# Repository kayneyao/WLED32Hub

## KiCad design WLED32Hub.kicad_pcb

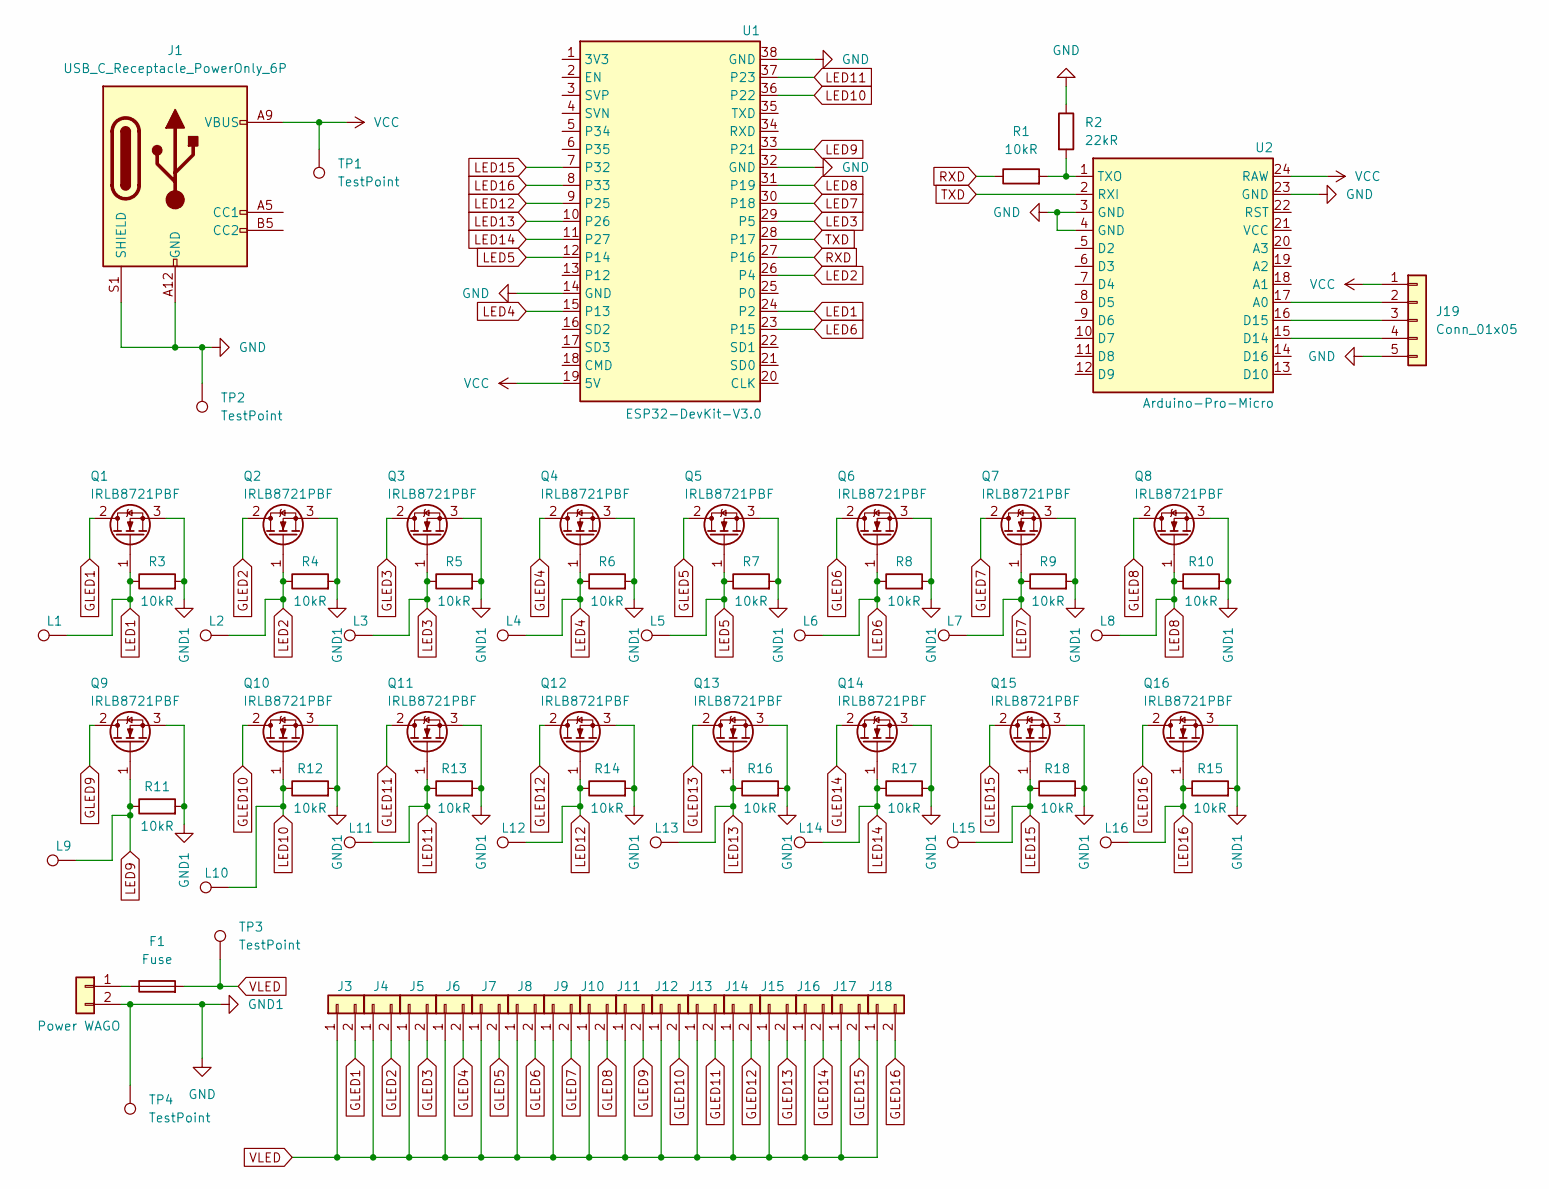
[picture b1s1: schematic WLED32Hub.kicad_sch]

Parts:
F1: Fuse; Fuseholder_Blade_ATO_Littelfuse_Pudenz_2_Pin
J1: USB_C_Receptacle_PowerOnly_6P; USB_C_Receptacle_GCT_USB4125-xx-x-0190_6P_TopMnt_Horizontal
J2: Power WAGO; WAGO_2606-1102
J3, J4, J5, J6, J7, J8, J9, J10, J11, J12, J13, J14, J15, J16, J17, J18: WAGO; TerminalBlock_WAGO_2601-1102_1x02_P3.50mm_Horizontal
J19: Conn_01x05; SolderWirePad_1x05_SMD_1x2mm
L1, L2, L3, L4, L5, L6, L7, L8, L9, L10, L11, L12, L13, L14, L15, L16: TestPoint; TestPoint_Pad_1.5x1.5mm
Q1, Q2, Q3, Q4, Q5, Q6, Q7, Q8, Q9, Q10, Q11, Q12, Q13, Q14, Q15, Q16: IRLB8721PBF; TO-220-3_Vertical
R1, R3, R4, R5, R6, R7, R8, R9, R10, R11, R12, R13, R14, R15, R16, R17, R18: 10kR; R_Axial_DIN0309_L9.0mm_D3.2mm_P12.70mm_Horizontal
R2: 22kR; R_Axial_DIN0309_L9.0mm_D3.2mm_P12.70mm_Horizontal
TP1, TP2, TP3, TP4: TestPoint; TestPoint_Pad_1.5x1.5mm
U1: ESP32-DevKit-V3.0; ESP32_DevKit_V3.0
U2: Arduino-Pro-Micro; Arduino_Pro_Micro

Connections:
GLED1: J3.2, Q1.2 (D)
GLED2: J4.2, Q2.2 (D)
GLED3: J5.2, Q3.2 (D)
GLED4: J6.2, Q4.2 (D)
GLED5: J7.2, Q5.2 (D)
GLED6: J8.2, Q6.2 (D)
GLED7: J9.2, Q7.2 (D)
GLED8: J10.2, Q8.2 (D)
GLED9: J11.2, Q9.2 (D)
GLED10: J12.2, Q10.2 (D)
GLED11: J13.2, Q11.2 (D)
GLED12: J14.2, Q12.2 (D)
GLED13: J15.2, Q13.2 (D)
GLED14: J16.2, Q14.2 (D)
GLED15: J17.2, Q15.2 (D)
GLED16: J18.2, Q16.2 (D)
GND: J1.A12 (GND), J1.B12 (GND), J1.S1 (SHIELD), J2.2, J19.5, Q1.3 (S), Q2.3 (S), Q3.3 (S), Q4.3 (S), Q5.3 (S), Q6.3 (S), Q7.3 (S), Q8.3 (S), Q9.3 (S), Q10.3 (S), Q11.3 (S), Q12.3 (S), Q13.3 (S), Q14.3 (S), Q15.3 (S), Q16.3 (S), R2.1, R3.2, R4.2, R5.2, R6.2, R7.2, R8.2, R9.2, R10.2, R11.2, R12.2, R13.2, R14.2, R15.2, R16.2, R17.2, R18.2, TP2.1, TP4.1, U1.14 (GND), U1.32 (GND), U1.38 (GND), U2.3 (GND), U2.4 (GND), U2.23 (GND); also elsewhere on the board
LED1: L1.1, Q1.1 (G), R3.1, U1.24 (P2)
LED2: L2.1, Q2.1 (G), R4.1, U1.26 (P4)
LED3: L3.1, Q3.1 (G), R5.1, U1.29 (P5)
LED4: L4.1, Q4.1 (G), R6.1, U1.15 (P13)
LED5: L5.1, Q5.1 (G), R7.1, U1.12 (P14)
LED6: L6.1, Q6.1 (G), R8.1, U1.23 (P15)
LED7: L7.1, Q7.1 (G), R9.1, U1.30 (P18)
LED8: L8.1, Q8.1 (G), R10.1, U1.31 (P19)
LED9: L9.1, Q9.1 (G), R11.1, U1.33 (P21)
LED10: L10.1, Q10.1 (G), R12.1, U1.36 (P22)
LED11: L11.1, Q11.1 (G), R13.1, U1.37 (P23)
LED12: L12.1, Q12.1 (G), R14.1, U1.9 (P25)
LED13: L13.1, Q13.1 (G), R16.1, U1.10 (P26)
LED14: L14.1, Q14.1 (G), R17.1, U1.11 (P27)
LED15: L15.1, Q15.1 (G), R18.1, U1.7 (P32)
LED16: L16.1, Q16.1 (G), R15.1, U1.8 (P33)
unnamed: F1.1, J2.1
unnamed: J19.2, U2.17 (A0)
unnamed: J19.3, U2.16 (D15)
unnamed: J19.4, U2.15 (D14)
unnamed: R1.2, R2.2, U2.1 (TXO)
RXD: R1.1, U1.27 (P16)
TXD: U1.28 (P17), U2.2 (RXI)
VCC: J1.A9 (VBUS), J1.B9 (VBUS), J19.1, TP1.1, U1.19 (5V), U2.24 (RAW)
VLED: F1.2, J3.1, J4.1, J5.1, J6.1, J7.1, J8.1, J9.1, J10.1, J11.1, J12.1, J13.1, J14.1, J15.1, J16.1, J17.1, J18.1, TP3.1; also elsewhere on the board

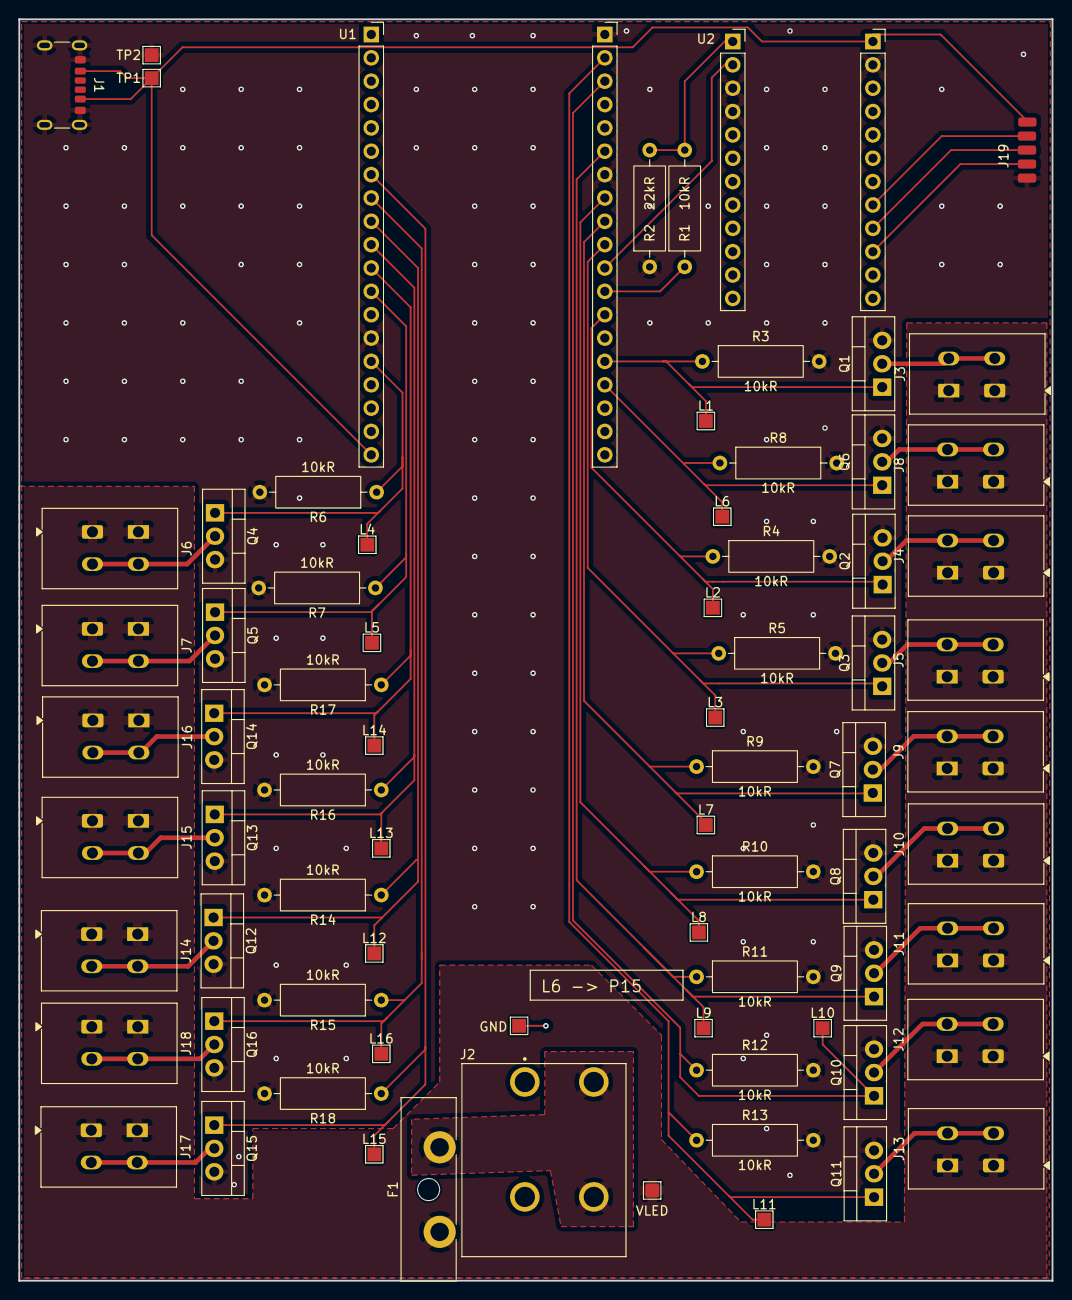
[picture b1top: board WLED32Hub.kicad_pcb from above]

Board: 2 copper layers, 112.4 x 137.2 mm, 76 parts (0 on the bottom side), 42 nets.

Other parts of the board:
GND: TestPoint; TestPoint_Pad_1.5x1.5mm
VLED: TestPoint; TestPoint_Pad_1.5x1.5mm

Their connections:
GND: GND.1; also elsewhere on the board
VLED: VLED.1; also elsewhere on the board

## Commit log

2025-05-31 Complete Schematic
2025-06-06 Connect LED 4
2025-06-06 Create & Assign all Footprints
2025-06-06 Add Components to PCB
2025-06-09 Adding Test Points to LED Switching Signals
2025-06-09 Silkscreen Markers + Test Point Connections
2025-06-09 Fix DRC and Connection Errors
